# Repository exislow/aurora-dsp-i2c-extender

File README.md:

# Aurora DSP I2C Extender

Original idea and almost exact copy source: https://www.diy-hifi-forum.eu/forum/showthread.php?21432-Adapter-f%FCr-FreeDSP-Expansion-(X102)-Schaltnetzteil-Filter

The only difference: It is open source.

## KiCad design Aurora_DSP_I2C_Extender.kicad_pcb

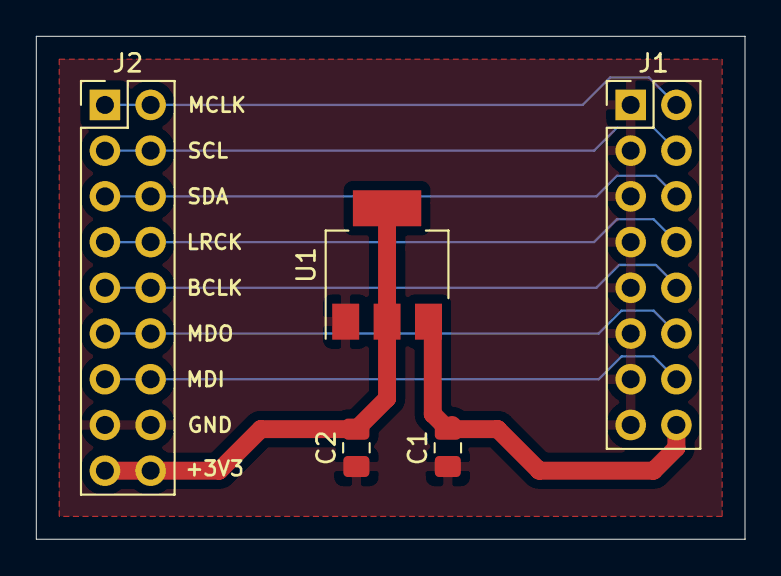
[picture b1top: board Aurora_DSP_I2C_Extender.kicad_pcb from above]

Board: 4 copper layers, 39.4 x 27.9 mm, 5 parts (0 on the bottom side), 10 nets.

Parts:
C1: 10uF; C_0805_2012Metric_Pad1.18x1.45mm_HandSolder
C2: 22uF; C_0805_2012Metric_Pad1.18x1.45mm_HandSolder
J1: Conn_02x08_Odd_Even; PinHeader_2x08_P2.54mm_Vertical
J2: Conn_02x09_Odd_Even; PinHeader_2x09_P2.54mm_Vertical
U1: AZ1117-3.3; SOT-223-3_TabPin2

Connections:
+3V3: C2.2, J2.17, J2.18, U1.2
+12V: C1.2, J1.16, U1.3
/BCLK: J1.10, J2.9, J2.10
/LRCK: J1.8, J2.7, J2.8
/MCLK: J1.2, J2.1, J2.2
/MDI: J1.14, J2.13, J2.14
/MDO: J1.12, J2.11, J2.12
/SCL: J1.4, J2.3, J2.4
/SDA: J1.6, J2.5, J2.6
GND: C1.1, C2.1, J1.1, J1.3, J1.5, J1.7, J1.9, J1.11, J1.13, J1.15, J2.15, J2.16, U1.1

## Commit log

2021-05-15 Initial commit.
